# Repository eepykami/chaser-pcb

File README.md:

# blinky
Little pin-sized, battery-powered PCB to make a few LEDs go blinky. Using an ATTINY13A microcontroller, and a CR2032 coin cell.

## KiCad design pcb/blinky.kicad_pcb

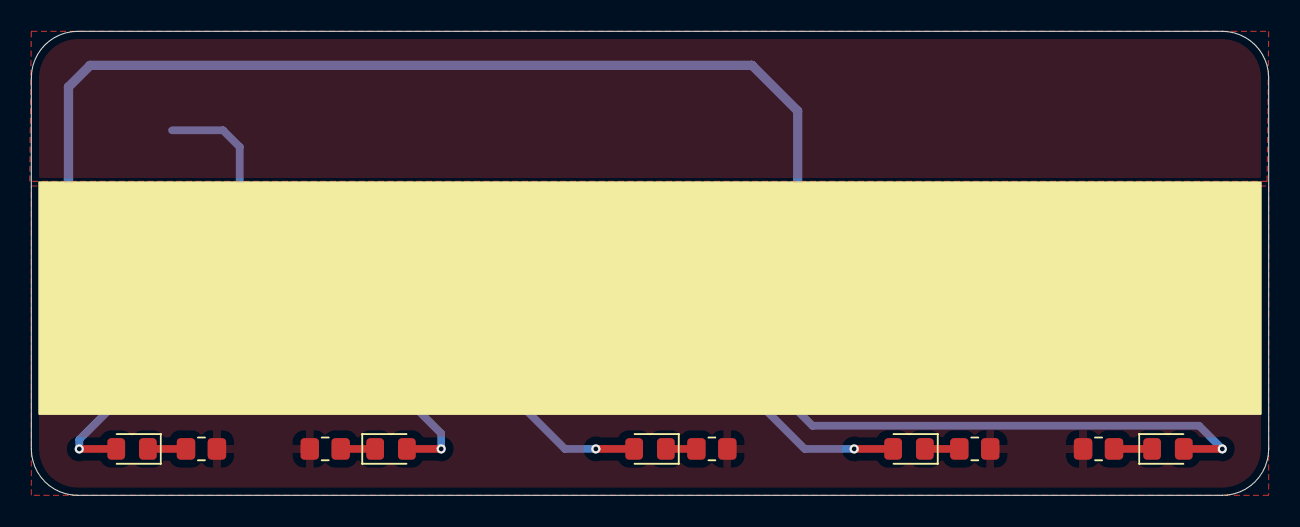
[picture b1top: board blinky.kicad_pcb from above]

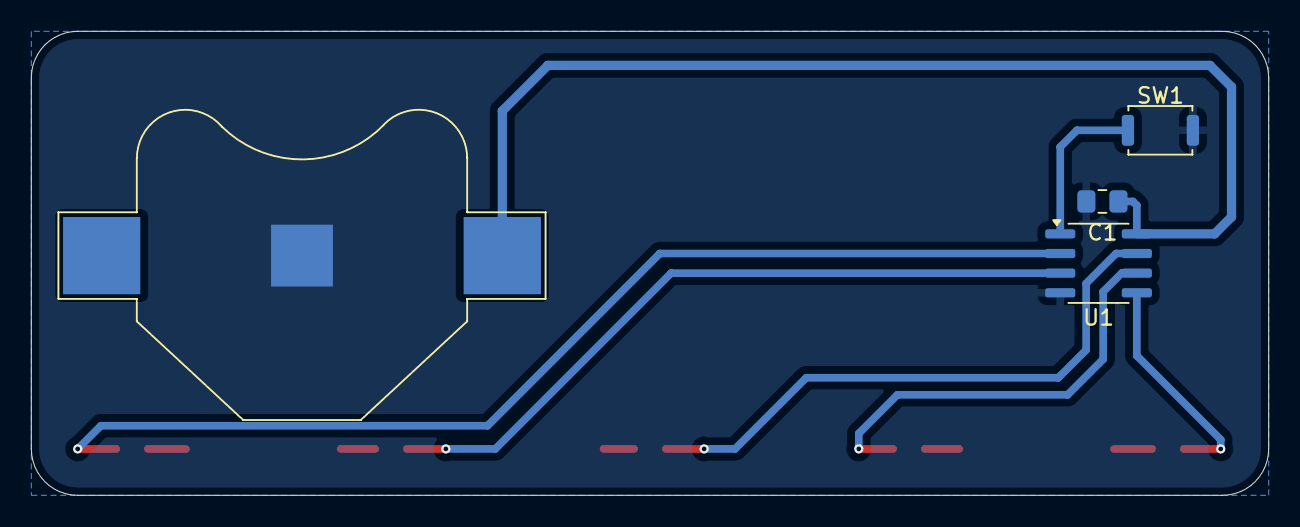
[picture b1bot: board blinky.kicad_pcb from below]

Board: 2 copper layers, 80.0 x 30.0 mm, 14 parts (4 on the bottom side), 13 nets.

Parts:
BT1: Battery_Cell; BatteryHolder_Multicomp_BC-2001_1x2032
C1: 0.1u; C_0805_2012Metric_Pad1.18x1.45mm_HandSolder
D1, D2, D3, D4, D5: LED; LED_0805_2012Metric_Pad1.15x1.40mm_HandSolder
R1, R2, R3, R4, R5: R; R_0805_2012Metric_Pad1.20x1.40mm_HandSolder
SW1: SW_Push; SW_Push_SPST_NO_Alps_SKRK
U1: ATtiny13A-SS; SOIC-8_3.9x4.9mm_P1.27mm

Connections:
+BATT: BT1.1 (+), C1.1, U1.8 (VCC)
GND: BT1.2 (-), C1.2, R1.2, R2.2, R3.2, R4.2, R5.2, SW1.2, U1.4 (GND)
unnamed: D1.2 (A), U1.5 (PB0)
unnamed: D1.1 (K), R1.1
unnamed: D2.2 (A), U1.6 (PB1)
unnamed: D2.1 (K), R2.1
unnamed: D3.2 (A), U1.7 (PB2)
unnamed: D3.1 (K), R3.1
unnamed: D4.2 (A), U1.3 (PB4)
unnamed: D4.1 (K), R4.1
unnamed: D5.2 (A), U1.2 (PB3)
unnamed: D5.1 (K), R5.1
unnamed: SW1.1, U1.1 (~RESET/PB5)

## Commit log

2024-04-09 Add initial folder structure
2024-04-09 Add code for project
2024-05-05 Move code to Microchip Studio, and start PCB work
2024-05-05 Remove redundant folder
